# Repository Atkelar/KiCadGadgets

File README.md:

# KiCadGadgets
Some misc projects made in KiCad that didn't require individual repositories...

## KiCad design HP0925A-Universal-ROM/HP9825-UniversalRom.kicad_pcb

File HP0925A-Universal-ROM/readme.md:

# Universal ROM Cartridge

This project is a KiCAD drawing for a universal ROM cartridge. It consists of address latches and decoders, a DIP switch block and two EEPROMs. The idea is to have all the option ROMs that the 9825 had on one cartridge - pretty much like the "B" model had - but still inside the regular expansion slot. This way, one can "emulate" any configuration of option ROMs at the push of a button....

## challenges...

After finally getting the "card enable" line set up correct in "Rev.B", I still couldn't get it to work. And even reading back the ROM had all sorts of weird results... 

 1. the first problem was my ROM reader adapter... I hooked up the IDA-Bits 8-15 in reverse, so naturally, the results were a bit... fragmented.

 2. the second issue is pretty much caused by HP. They have put a set of bus transceivers in between the system IDA bus and the expansion slots. Those decouple all 16 IDA bus lines, but all other signals are passed in "as is". No bit deal. But somewhere it seems to have gotten lost, that these are INVERTING TRANSCEIVERS! So both address and data arrive and go out from the option ROMs in a "positive logic" fashion. I set up my ROMs to handle the reversed and inverted bit pattern that the system ROM needs, so again: didn't *quite* work as expected. And that took some time to find out...

Anyhow: it works now! My system is running on an almost full complement of ROM cartridges! All I'm missing is the "mass storage" (aka "disk IO") ROM... anybody got a source of that somewhere?

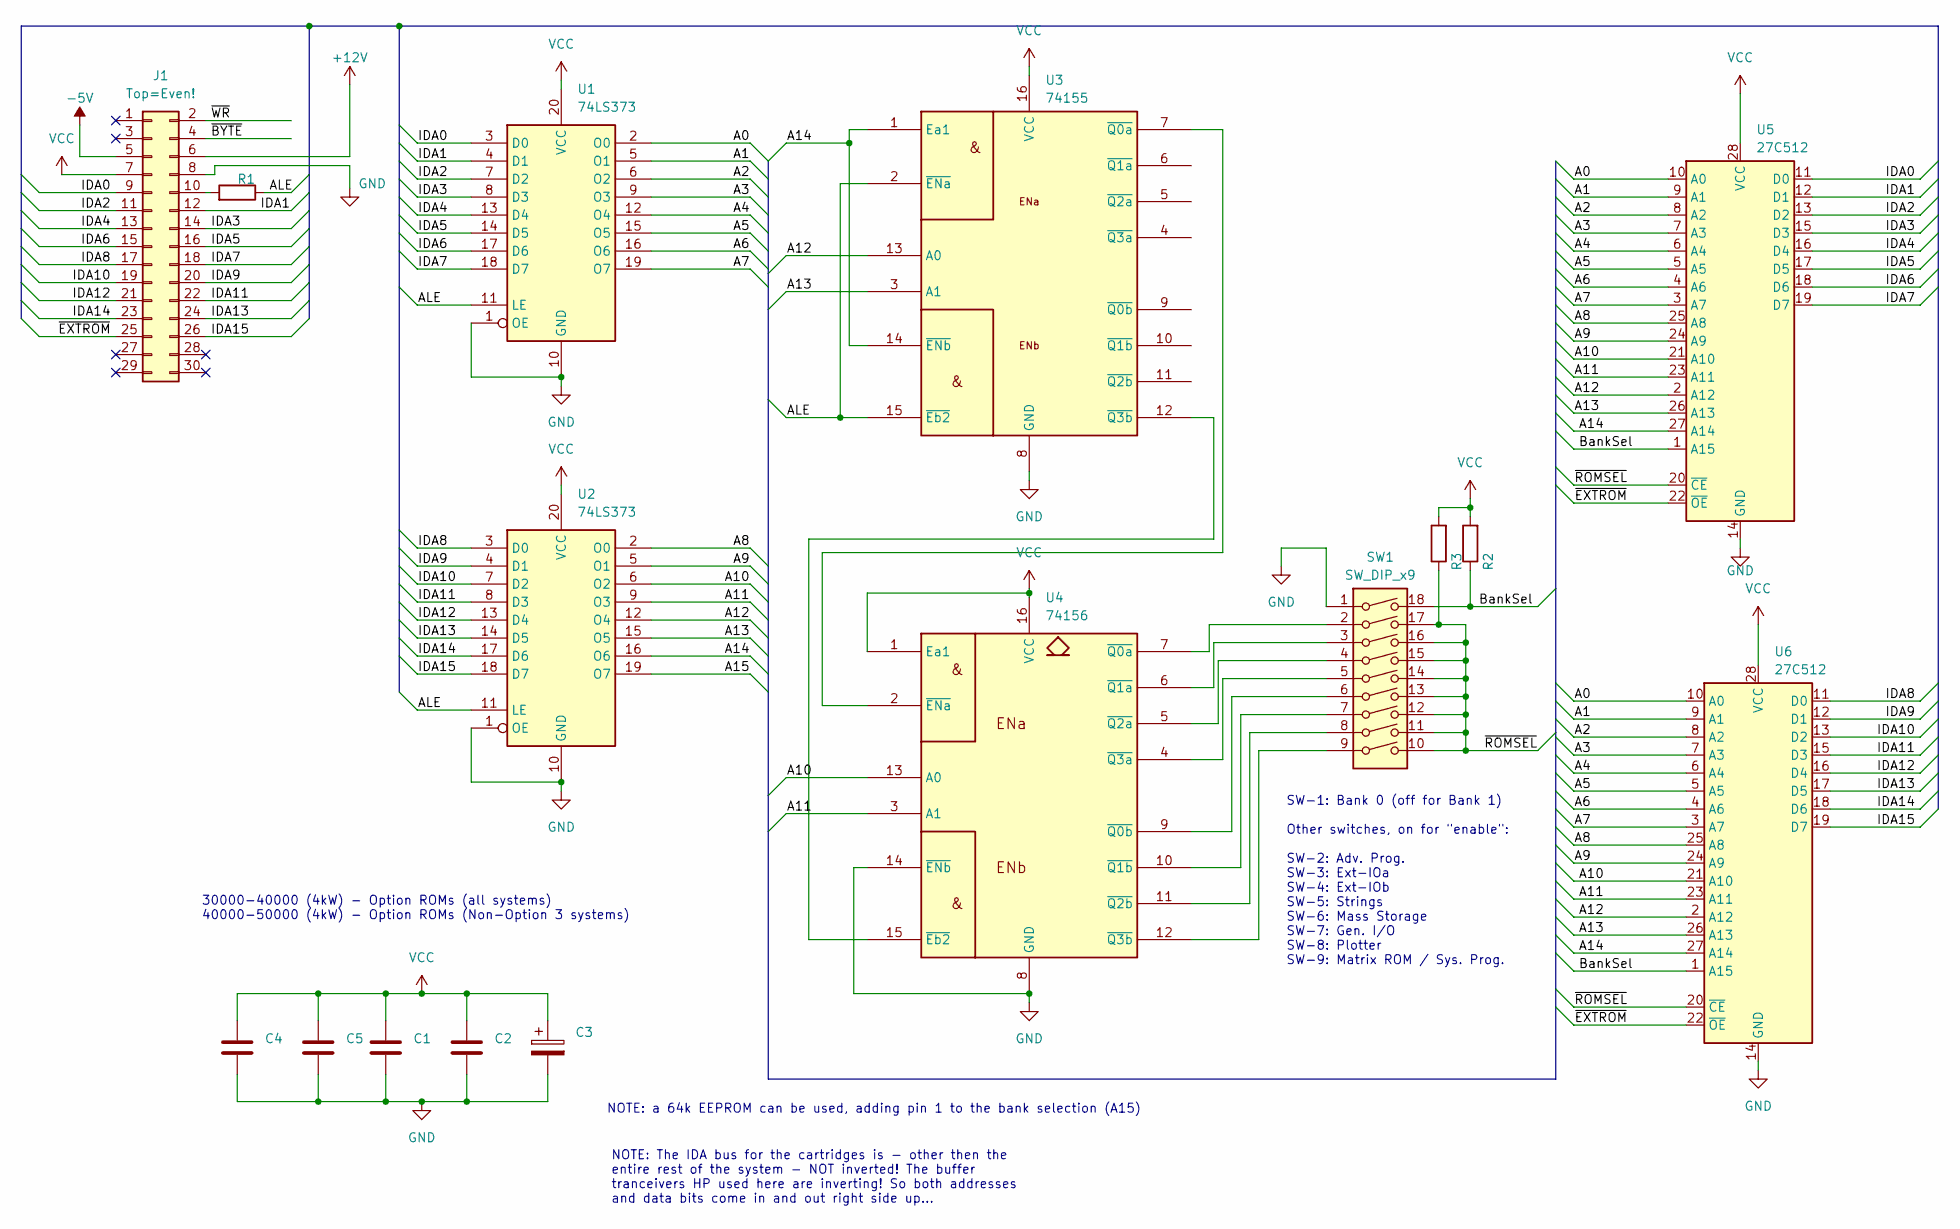
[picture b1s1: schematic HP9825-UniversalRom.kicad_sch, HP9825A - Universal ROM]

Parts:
C1, C2, C4, C5: C; C_Disc_D5.1mm_W3.2mm_P5.00mm
C3: CP_Axial_L11.0mm_D5.0mm_P18.00mm_Horizontal
J1: Top=Even!; 9825A-MemoryModule
R1: 16; R_Axial_DIN0207_L6.3mm_D2.5mm_P10.16mm_Horizontal
R2, R3: 3k3; R_Axial_DIN0207_L6.3mm_D2.5mm_P10.16mm_Horizontal
SW1: SW_DIP_x9; SW_DIP_SPSTx09_Slide_6.7x24.42mm_W7.62mm_P2.54mm_LowProfile
U1, U2: 74LS373; DIP-20_W7.62mm
U3: 74155; DIP-16_W7.62mm
U4: 74156; DIP-16_W7.62mm
U5, U6: 27C512; DIP-28_W15.24mm

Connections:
+12V: J1.6
-5V: J1.5
/A0: U1.2 (O0), U5.10 (A0), U6.10 (A0)
/A1: U1.5 (O1), U5.9 (A1), U6.9 (A1)
/A2: U1.6 (O2), U5.8 (A2), U6.8 (A2)
/A3: U1.9 (O3), U5.7 (A3), U6.7 (A3)
/A4: U1.12 (O4), U5.6 (A4), U6.6 (A4)
/A5: U1.15 (O5), U5.5 (A5), U6.5 (A5)
/A6: U1.16 (O6), U5.4 (A6), U6.4 (A6)
/A7: U1.19 (O7), U5.3 (A7), U6.3 (A7)
/A8: U2.2 (O0), U5.25 (A8), U6.25 (A8)
/A9: U2.5 (O1), U5.24 (A9), U6.24 (A9)
/A10: U2.6 (O2), U4.13 (A0), U5.21 (A10), U6.21 (A10)
/A11: U2.9 (O3), U4.3 (A1), U5.23 (A11), U6.23 (A11)
/A12: U2.12 (O4), U3.13 (A0), U5.2 (A12), U6.2 (A12)
/A13: U2.15 (O5), U3.3 (A1), U5.26 (A13), U6.26 (A13)
/A14: U2.16 (O6), U3.1 (Ea1), U3.14 (~ENb), U5.27 (A14), U6.27 (A14)
/A15: U2.19 (O7)
/ALE: R1.1, U1.11 (LE), U2.11 (LE), U3.2 (~ENa), U3.15 (~Eb2)
/BankSel: R2.1, SW1.18, U5.1 (A15), U6.1 (A15)
/IDA0: J1.9, U1.3 (D0), U5.11 (D0)
/IDA1: J1.12, U1.4 (D1), U5.12 (D1)
/IDA2: J1.11, U1.7 (D2), U5.13 (D2)
/IDA3: J1.14, U1.8 (D3), U5.15 (D3)
/IDA4: J1.13, U1.13 (D4), U5.16 (D4)
/IDA5: J1.16, U1.14 (D5), U5.17 (D5)
/IDA6: J1.15, U1.17 (D6), U5.18 (D6)
/IDA7: J1.18, U1.18 (D7), U5.19 (D7)
/IDA8: J1.17, U2.3 (D0), U6.11 (D0)
/IDA9: J1.20, U2.4 (D1), U6.12 (D1)
/IDA10: J1.19, U2.7 (D2), U6.13 (D2)
/IDA11: J1.22, U2.8 (D3), U6.15 (D3)
/IDA12: J1.21, U2.13 (D4), U6.16 (D4)
/IDA13: J1.24, U2.14 (D5), U6.17 (D5)
/IDA14: J1.23, U2.17 (D6), U6.18 (D6)
/IDA15: J1.26, U2.18 (D7), U6.19 (D7)
/~BYTE: J1.4
/~EXTROM: J1.25, U5.22 (~OE), U6.22 (~OE)
/~ROMSEL: R3.1, SW1.10, SW1.11, SW1.12, SW1.13, SW1.14, SW1.15, SW1.16, SW1.17, U5.20 (~CE), U6.20 (~CE)
/~WR: J1.2
GND: C1.2, C2.2, C3.2, C4.2, C5.2, J1.8, SW1.1, U1.1 (OE), U1.10 (GND), U2.1 (OE), U2.10 (GND), U3.8 (GND), U4.8 (GND), U4.14 (~ENb), U5.14 (GND), U6.14 (GND)
unnamed: J1.10, R1.2
unnamed: U3.7 (~Q0a), U4.2 (~ENa)
unnamed: U3.12 (~Q3b), U4.15 (~Eb2)
unnamed: SW1.2, U4.7 (~Q0a)
unnamed: SW1.6, U4.9 (~Q0b)
unnamed: SW1.3, U4.6 (~Q1a)
unnamed: SW1.7, U4.10 (~Q1b)
unnamed: SW1.4, U4.5 (~Q2a)
unnamed: SW1.8, U4.11 (~Q2b)
unnamed: SW1.5, U4.4 (~Q3a)
unnamed: SW1.9, U4.12 (~Q3b)
VCC: C1.1, C2.1, C3.1, C4.1, C5.1, J1.7, R2.2, R3.2, U1.20 (VCC), U2.20 (VCC), U3.16 (VCC), U4.1 (Ea1), U4.16 (VCC), U5.28 (VCC), U6.28 (VCC)

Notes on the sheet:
30000-40000 (4kW) - Option ROMs (all systems) 40000-50000 (4kW) - Option ROMs (Non-Option 3 systems)
NOTE: a 64k EEPROM can be used, adding pin 1 to the bank selection (A15)
SW-1: Bank 0 (off for Bank 1) Other switches, on for "enable": SW-2: Adv. Prog. SW-3: Ext-IOa SW-4: Ext-IOb SW-5: Strings SW-6: Mass Storage SW-7: Gen. I/O SW-8: Plotter SW-9: Matrix ROM / Sys. Prog.
NOTE: The IDA bus for the cartridges is - other then the entire rest of the system - NOT inverted! The buffer tranceivers HP used here are inverting! So both addresses and data bits come in and out right side up...

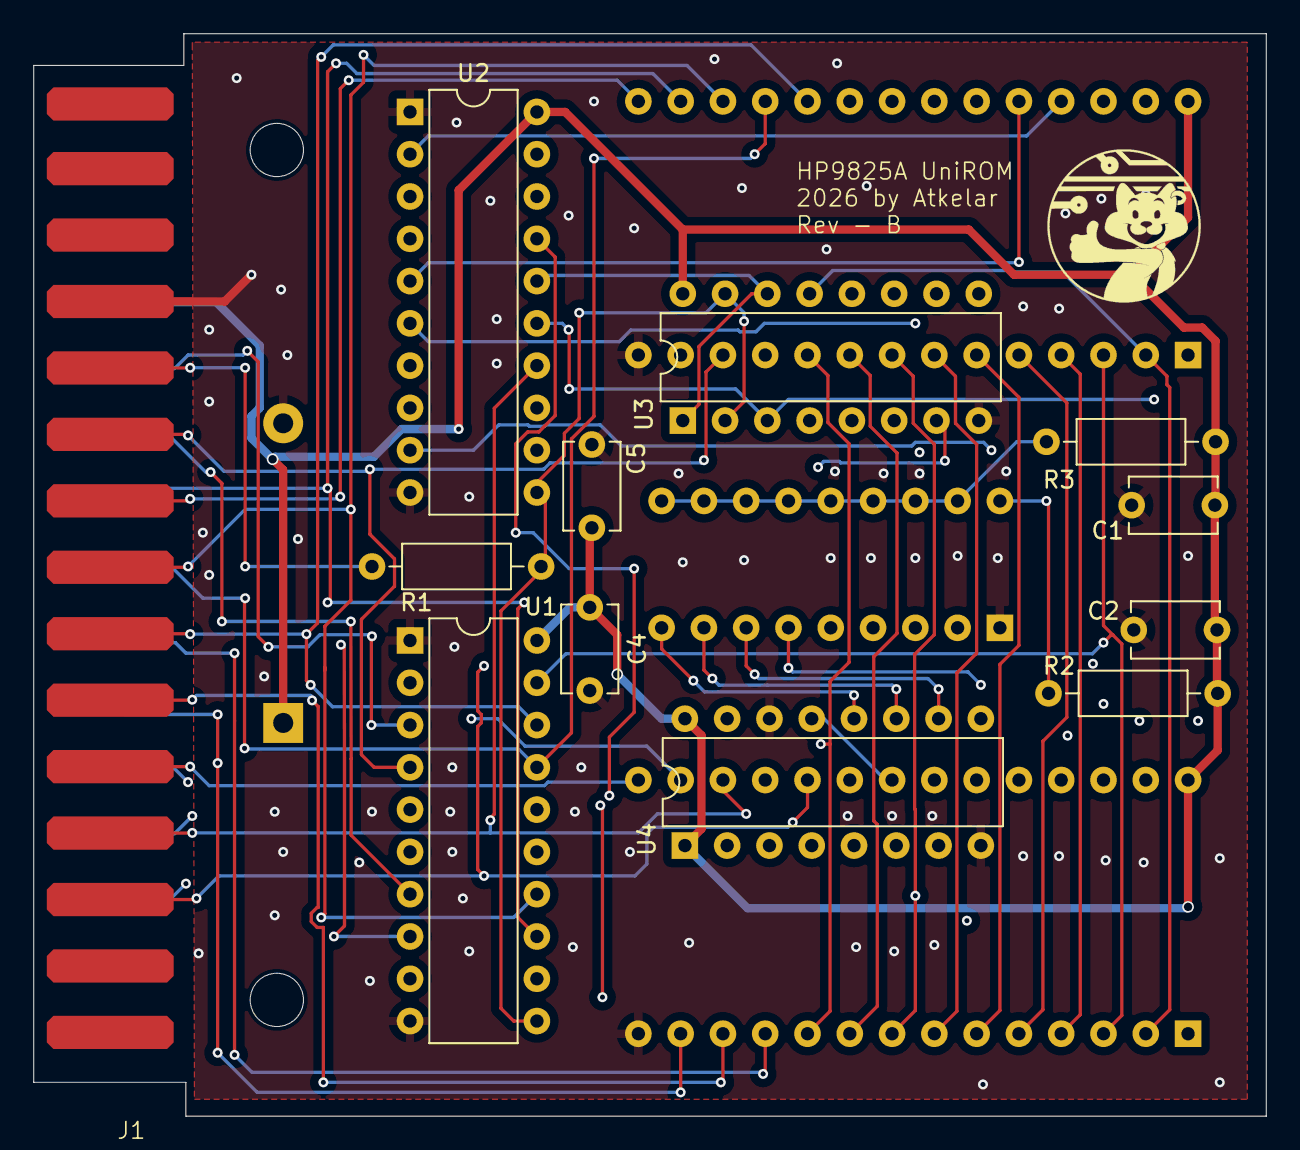
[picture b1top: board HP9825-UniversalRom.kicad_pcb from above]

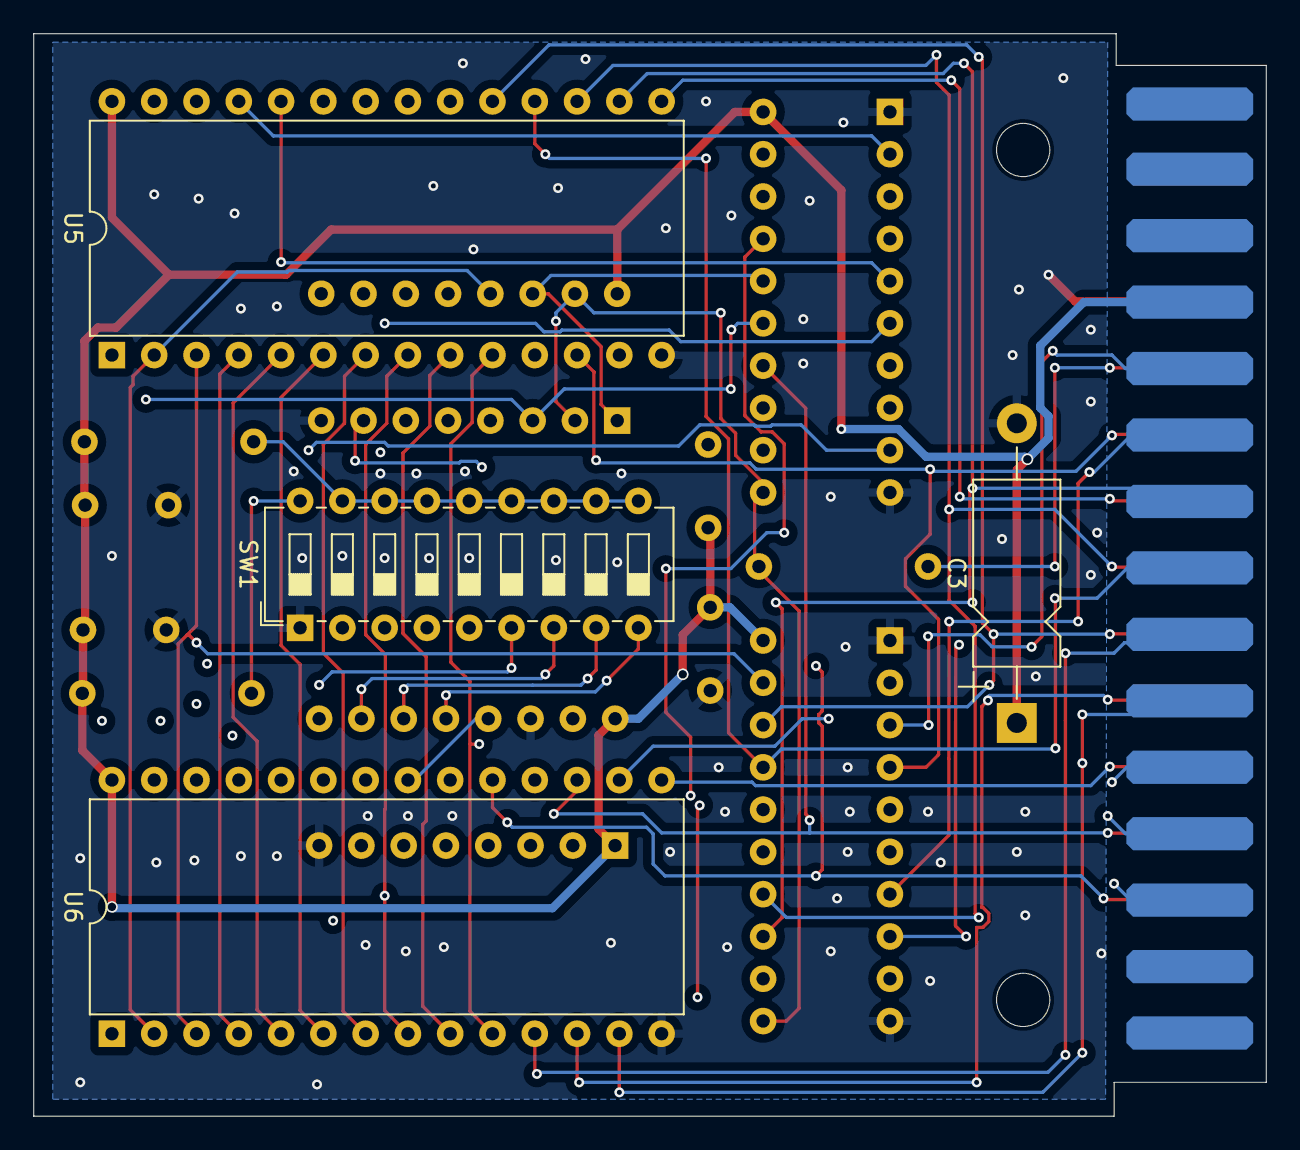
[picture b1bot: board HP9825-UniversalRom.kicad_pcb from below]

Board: 4 copper layers, 74.0 x 65.0 mm, 16 parts (4 on the bottom side), 48 nets.

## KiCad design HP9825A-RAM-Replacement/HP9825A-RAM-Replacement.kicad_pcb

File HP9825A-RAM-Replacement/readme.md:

# HP9825A RAM Replacement

The HP9825A "calculator"[^1] is a pretty useful machine for controlling various lab related devices, mostly but not exclusively vie the HP-IB bus. When it originally was designed, it came with a base contingent of 8k of RAM, arranged in 4k words. For a calculator that is controlling a few measurements, this seemed plenty. But naturally, requirements grew and so even the base unit offered expansions to 16k or even 24k of RAM, by means of adding a second 8k or 16k RAM PCB to the existing 8k one. Problematic here is that these RAM chips are DRAMs that are aging by now and getting hard to replace. Mostly because while the are using a 5V operating voltage, they want their CS line driven by 12V and also need a -5V bias voltage. These type of chips haven't been made in ages. Another quirk is that they have inputs and outputs on different pins *AND* different polarity: i.e. the input is normal the output is inverted. So between the chip and the bus needs to be a non-inverting buffer (or none at all) in one direction and an inverting one in the other, or else all the bits will appear flipped.

That being said: my own 9825 was acting a bit weird, even after I fixed one of the three RAM PCBs I had and while it was mostly working, it did show signs of instability. My toughts were: the RAM is going bad. Note that so far, this hasn't been confirmed yet; another possible issue presented itself but that is another project. The suspicion was just the motivation behind this project.

## Idea...

These days, we can get SRAM chips with 64k or more a dime a dozen almost. And they are fast enough to run at the 6MHz clock speed. So... why even use DRAM? Back in the day, it was mostly cost and power requirements. But when I look at the 400mA draw on the 12V rail that just hte chip select lines need... brrr! *ANY* modern SRAM will outperform these old chips by a longshot. And it would also eliminate the refresh logic required and possibly the refresh-collision wait states. So: win-win-win-win... I'll take it!

## Process...

Decoding the various schematic versions that are out there, along with the original patent and CPU documentation I'm pretty sure I have nailed down the way the memory cycle works and can confidentally rip out about 50% of the support chips that only deal with the refresh logic.

The latest circuit design went to the breadboard!

...and from there to a PCB prototype!

And: ta-da! It works!

Note that there is an unpopulated chip on the board... that is a leftover from the process that I missed; unused chip that got removed and I didn't remove it from the PCB. Whoops. Revision B here has that fixed.

## Configuration!

The address space of the 9825 is a 15-bit word space. I.e. 32k 2-byte addresses for a grand total of 64k byte. It's a bit of a twist to think in words when you are used to bytes, but this is how it works. Also, that memory space is strictly divided into the lower range for ROMs and the upper range for RAM. The CPU demands that the upper edge of addressable memory is RAM; it puts some floating point registeres there that can't be moved. The system ROM also puts all its core variables and the call stack there. This is why the upper 8k bytes are fixed on my replacement baord. It will *always* react to that. Then, you can add more 8k blocks from top to bottom to get 16, 24 and 32 kbytes of RAM. This setting has to be mirrored by the DIP switches on the CPU PCB, since those will prevent the "STM" signal to reach the RAM at all otherwise.

The important side note is: the expansion ROMs[^2] are hard coded to specific addresses. And that means that the 24kbyte version is the maximum RAM that can still use all the available expansion modules. The 32k version has a few no-go expansion modules and mixing these might cause damage to the circuitry. I'm keeping mine at 24k for that reason!

## Possible optimization?

I am not 100% sure if the "MEB" signal needs to be handled at all - it is "memory busy" I'd guess, to signal the CPU that the RAM isn't ready to process the request. It is tied to the refresh cycle and other elements, so I kept it. Since it's open collector, it should be easy enough to test: disconect the bus line and see if it still works, but right now, I'm too happy that it works at all to try something crazy like this!

[^1]: later model revisions did use the term "computer", but this is specifically for the base model "A", so I'll call it calculator anyhow
[^2]: which are a must have!

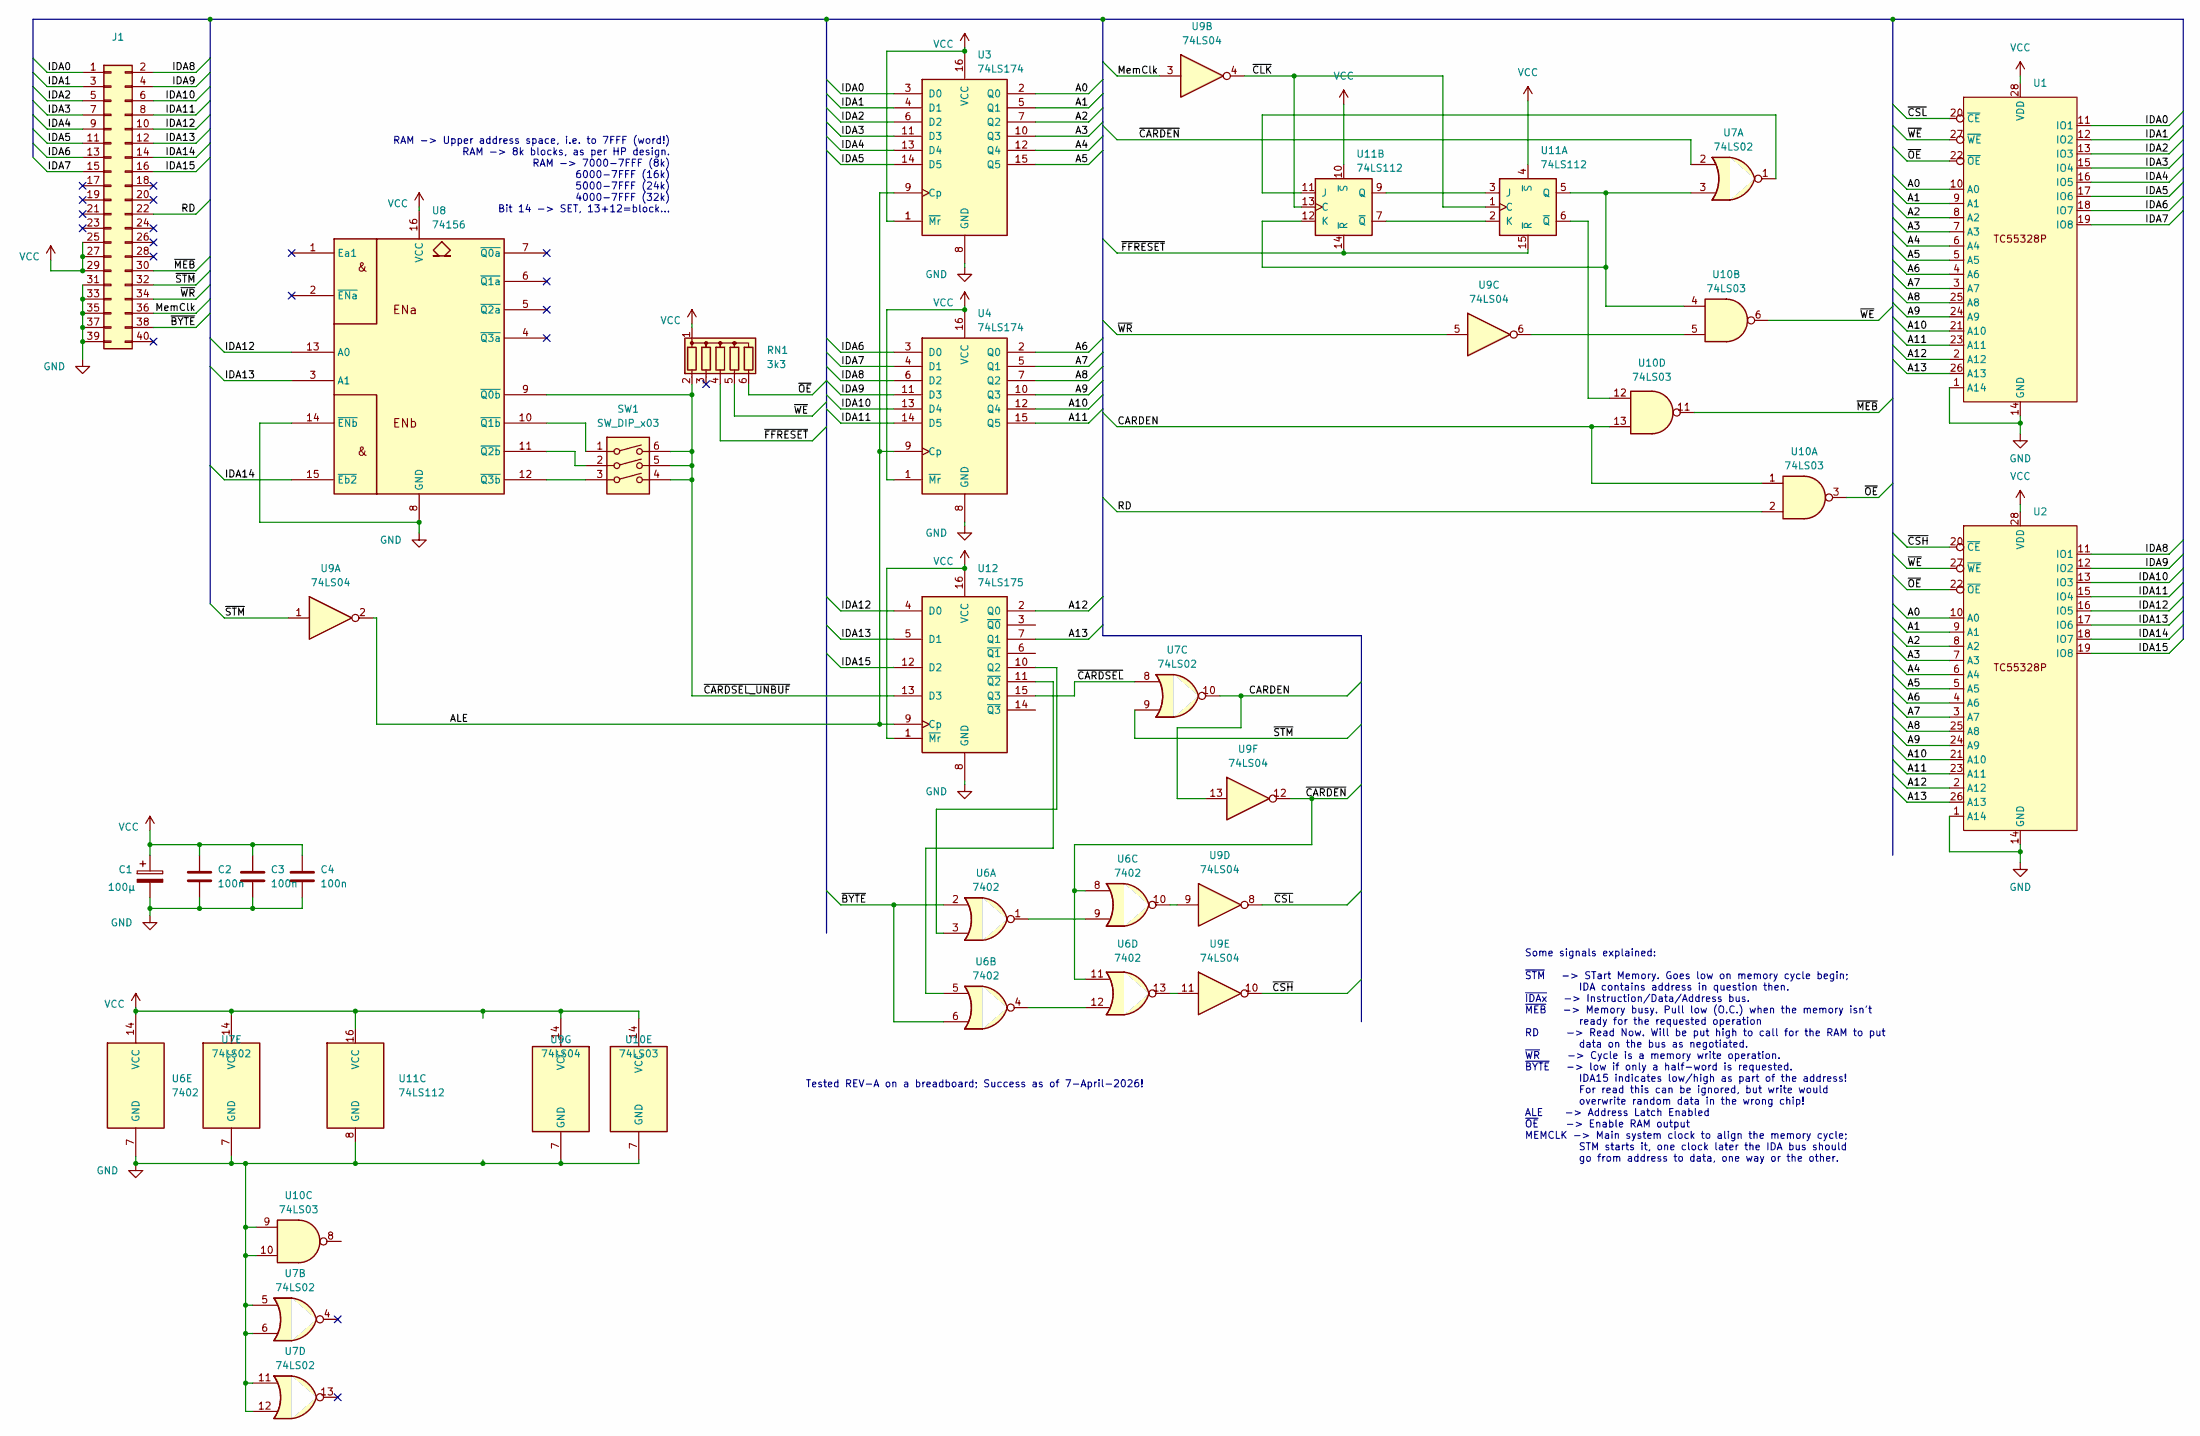
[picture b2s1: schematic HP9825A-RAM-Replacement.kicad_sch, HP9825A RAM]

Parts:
C1: 100µ; CP_Axial_L18.0mm_D10.0mm_P25.00mm_Horizontal
C2, C3, C4: 100n; C_Disc_D4.7mm_W2.5mm_P5.00mm
J1: Conn_02x20_Odd_Even; 9825A-RAM-CE
RN1: 3k3; R_Array_SIP6
SW1: SW_DIP_x03; SW_DIP_SPSTx03_Slide_9.78x9.8mm_W7.62mm_P2.54mm
U1, U2: DIP-28_W7.62mm
U3, U4: 74LS174; DIP-16_W7.62mm
U6: 7402; DIP-14_W7.62mm
U7: 74LS02; DIP-14_W7.62mm
U8: 74156; DIP-16_W7.62mm
U9: 74LS04; DIP-14_W7.62mm
U10: 74LS03; DIP-14_W7.62mm
U11: 74LS112; DIP-16_W7.62mm
U12: 74LS175; DIP-16_W7.62mm

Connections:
/A0: U1.10 (A0), U2.10 (A0), U3.2 (Q0)
/A1: U1.9 (A1), U2.9 (A1), U3.5 (Q1)
/A2: U1.8 (A2), U2.8 (A2), U3.7 (Q2)
/A3: U1.7 (A3), U2.7 (A3), U3.10 (Q3)
/A4: U1.6 (A4), U2.6 (A4), U3.12 (Q4)
/A5: U1.5 (A5), U2.5 (A5), U3.15 (Q5)
/A6: U1.4 (A6), U2.4 (A6), U4.2 (Q0)
/A7: U1.3 (A7), U2.3 (A7), U4.5 (Q1)
/A8: U1.25 (A8), U2.25 (A8), U4.7 (Q2)
/A9: U1.24 (A9), U2.24 (A9), U4.10 (Q3)
/A10: U1.21 (A10), U2.21 (A10), U4.12 (Q4)
/A11: U1.23 (A11), U2.23 (A11), U4.15 (Q5)
/A12: U1.2 (A12), U2.2 (A12), U12.2 (Q0)
/A13: U1.26 (A13), U2.26 (A13), U12.7 (Q1)
/ALE: U3.9 (Cp), U4.9 (Cp), U9.2, U12.9 (Cp)
/CARDEN: U7.10, U9.13, U10.1, U10.13
/IDA0: J1.1, U1.11 (IO1), U3.3 (D0)
/IDA1: J1.3, U1.12 (IO2), U3.4 (D1)
/IDA2: J1.5, U1.13 (IO3), U3.6 (D2)
/IDA3: J1.7, U1.15 (IO4), U3.11 (D3)
/IDA4: J1.9, U1.16 (IO5), U3.13 (D4)
/IDA5: J1.11, U1.17 (IO6), U3.14 (D5)
/IDA6: J1.13, U1.18 (IO7), U4.3 (D0)
/IDA7: J1.15, U1.19 (IO8), U4.4 (D1)
/IDA8: J1.2, U2.11 (IO1), U4.6 (D2)
/IDA9: J1.4, U2.12 (IO2), U4.11 (D3)
/IDA10: J1.6, U2.13 (IO3), U4.13 (D4)
/IDA11: J1.8, U2.15 (IO4), U4.14 (D5)
/IDA12: J1.10, U2.16 (IO5), U8.13 (A0), U12.4 (D0)
/IDA13: J1.12, U2.17 (IO6), U8.3 (A1), U12.5 (D1)
/IDA14: J1.14, U2.18 (IO7), U8.15 (~Eb2)
/IDA15: J1.16, U2.19 (IO8), U12.12 (D2)
/MemClk: J1.36, U9.3
/RD: J1.22, U10.2
/RDY: J1.30, U10.11
/~BYTE: J1.38, U6.2, U6.6
/~CARDEN: U6.8, U6.11, U7.2, U9.12
/~CARDSEL_UNBUF: RN1.2 (R1), SW1.4, SW1.5, SW1.6, U8.9 (~Q0b), U12.13 (D3)
/~CARDSEL: U7.8, U12.15 (Q3)
/~CLK: U9.4, U11.1 (C), U11.13 (C)
/~CSH: U2.20 (~CE), U9.10
/~CSL: U1.20 (~CE), U9.8
/~FFRESET: RN1.4 (R3), U11.14 (~R), U11.15 (~R)
/~OE: RN1.6 (R5), U1.22 (~OE), U2.22 (~OE), U10.3
/~STM: J1.32, U7.9, U9.1
/~WE: RN1.5 (R4), U1.27 (~WE), U2.27 (~WE), U10.6
/~WR: J1.34, U9.5
GND: C1.2, C2.2, C3.2, C4.2, J1.31, J1.33, J1.35, J1.37, J1.39, U1.1 (A14), U1.14 (GND), U2.1 (A14), U2.14 (GND), U3.8 (GND), U4.8 (GND), U6.7 (GND), U7.5, U7.6, U7.7 (GND), U7.11, U7.12, U8.8 (GND), U8.14 (~ENb), U9.7 (GND), U10.7 (GND), U10.9, U10.10, U11.8 (GND), U12.8 (GND)
unnamed: U6.1, U6.9
unnamed: U6.10, U9.9
unnamed: U6.4, U6.12
unnamed: U6.13, U9.11
unnamed: SW1.1, U8.10 (~Q1b)
unnamed: SW1.2, U8.11 (~Q2b)
unnamed: SW1.3, U8.12 (~Q3b)
unnamed: U9.6, U10.5
unnamed: U11.3 (J), U11.9 (Q)
unnamed: U11.2 (K), U11.7 (~Q)
unnamed: U7.3, U10.4, U11.5 (Q), U11.12 (K)
unnamed: U10.12, U11.6 (~Q)
unnamed: U7.1, U11.11 (J)
unnamed: U6.3, U12.10 (Q2)
unnamed: U6.5, U12.11 (~Q2)
VCC: C1.1, C2.1, C3.1, C4.1, J1.25, J1.27, J1.29, RN1.1 (common), U1.28 (VDD), U2.28 (VDD), U3.1 (~Mr), U3.16 (VCC), U4.1 (~Mr), U4.16 (VCC), U6.14 (VCC), U7.14 (VCC), U8.16 (VCC), U9.14 (VCC), U10.14 (VCC), U11.4 (~S), U11.10 (~S), U11.16 (VCC), U12.1 (~Mr), U12.16 (VCC)

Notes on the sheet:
RAM -> Upper address space, i.e. to 7FFF (word!) RAM -> 8k blocks, as per HP design. RAM -> 7000-7FFF (8k) 6000-7FFF (16k) 5000-7FFF (24k) 4000-7FFF (32k) Bit 14 -> SET, 13+12=block...
Tested REV-A on a breadboard; Success as of 7-April-2026!
Some signals explained: ~{STM} -> STart Memory. Goes low on memory cycle begin; IDA contains address in question then. ~{IDAx} -> Instruction/Data/Address bus. ~{MEB} -> Memory busy. Pull low (O.C.) when the memory isn't ready for the requested operation RD -> Read Now. Will be put high to call for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

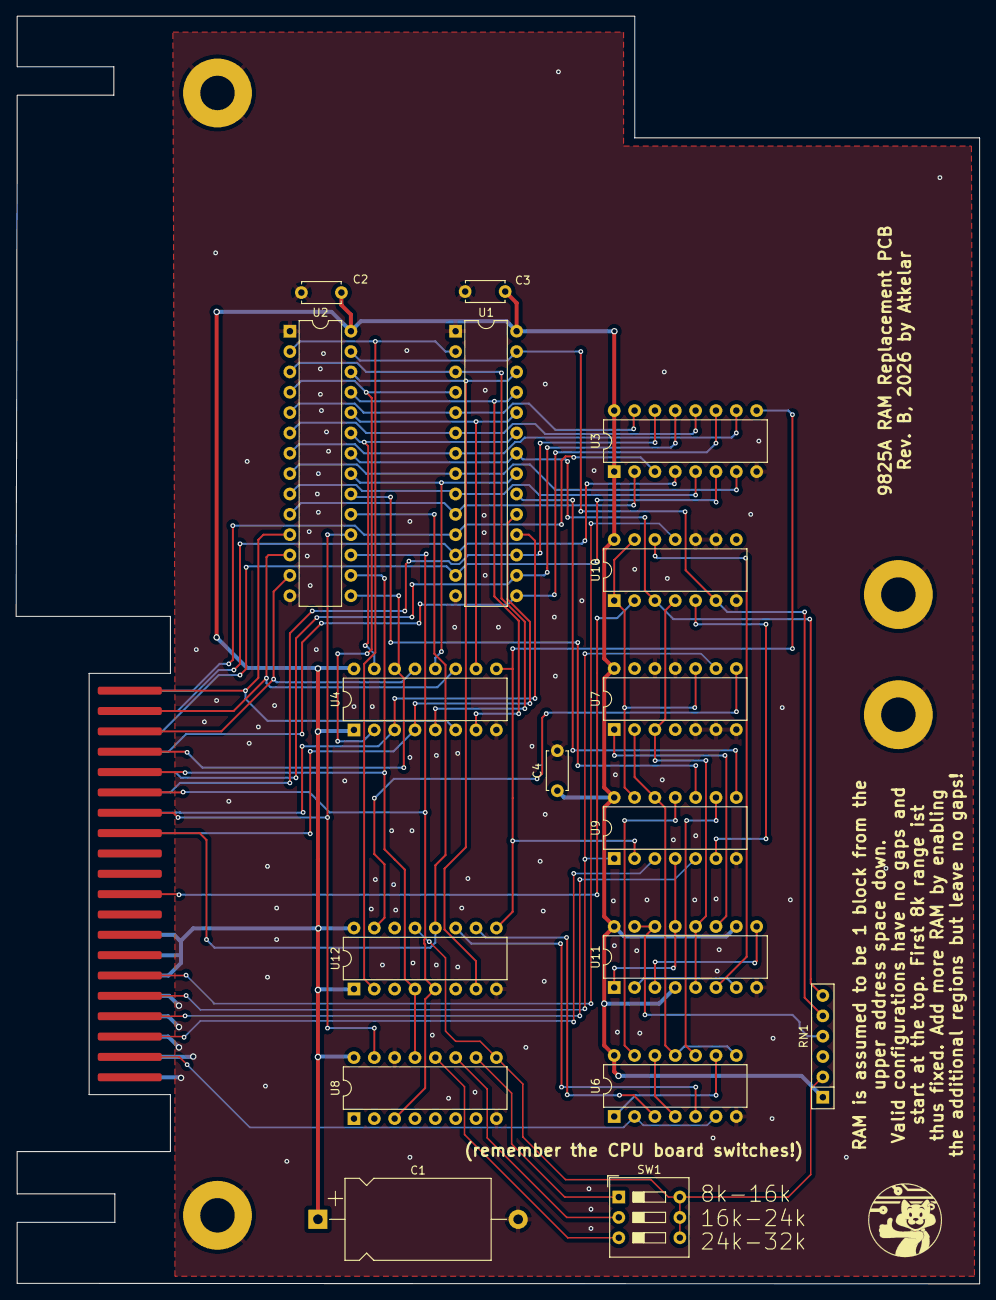
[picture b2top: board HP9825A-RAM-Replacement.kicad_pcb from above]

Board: 2 copper layers, 120.3 x 158.2 mm, 18 parts (0 on the bottom side), 64 nets.

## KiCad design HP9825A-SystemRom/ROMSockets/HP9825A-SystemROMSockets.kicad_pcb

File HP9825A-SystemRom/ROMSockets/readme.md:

# ROM Socket PCB

This PCB connects to the main PCB via 40-pin pin header, or just plain wires. It is required to offset the PCB to make room for the IC sockets and ROM chips.

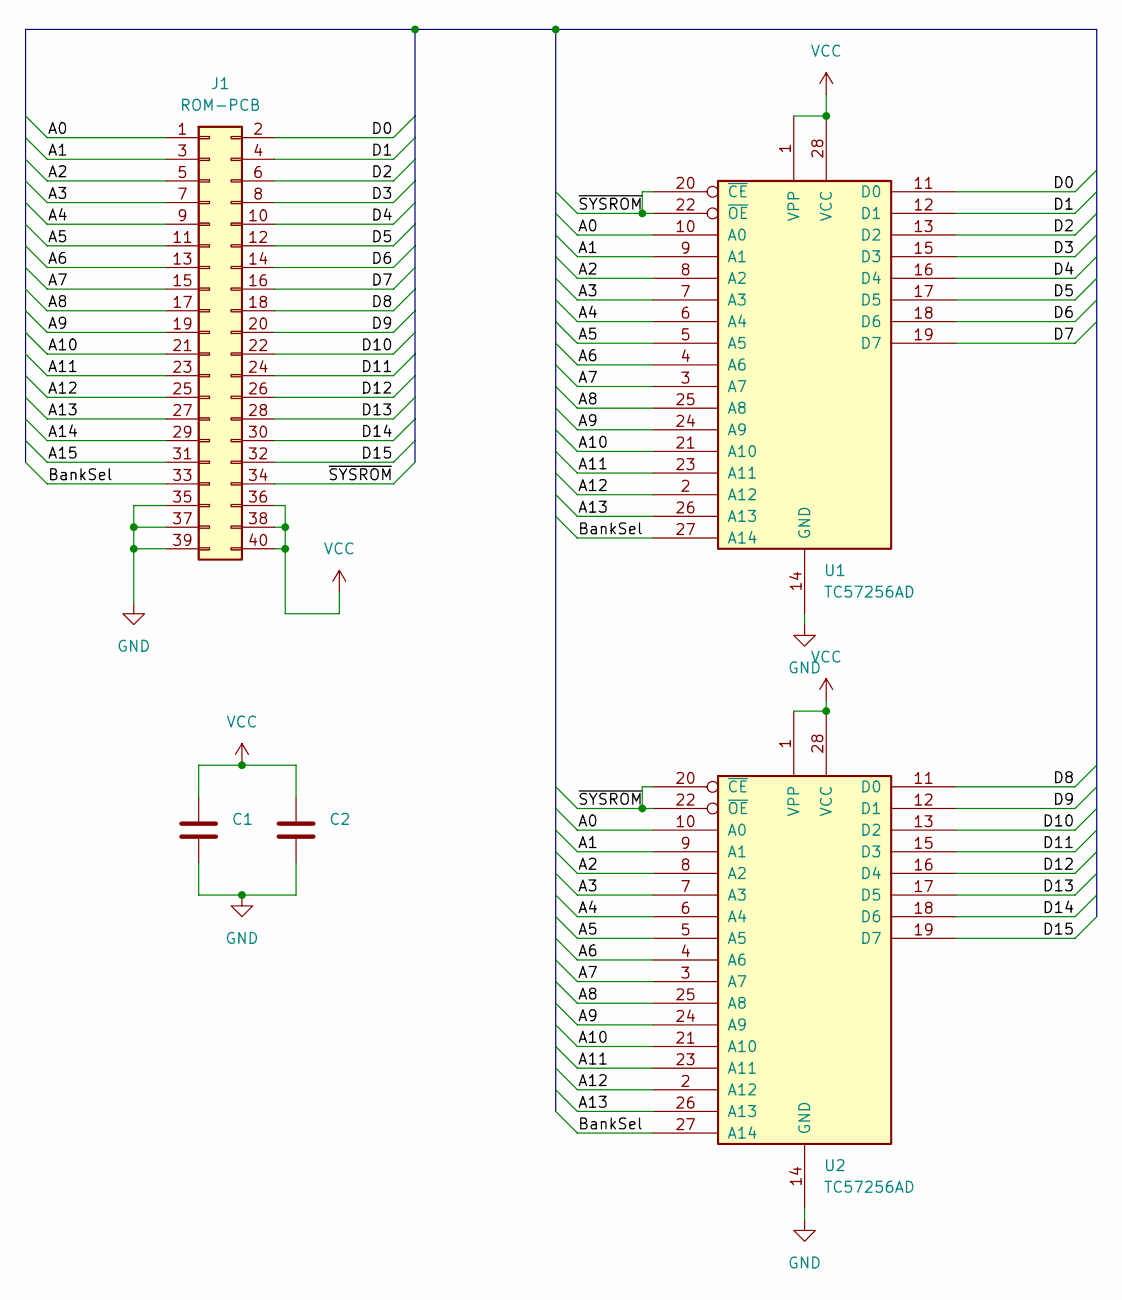
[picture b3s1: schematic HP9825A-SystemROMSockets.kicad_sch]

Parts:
C1, C2: C; C_Disc_D5.1mm_W3.2mm_P5.00mm
J1: ROM-PCB; PinHeader_2x20_P2.54mm_Vertical
U1, U2: TC57256AD; DIP-28_W15.24mm_LongPads

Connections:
/A0: J1.1, U1.10 (A0), U2.10 (A0)
/A1: J1.3, U1.9 (A1), U2.9 (A1)
/A2: J1.5, U1.8 (A2), U2.8 (A2)
/A3: J1.7, U1.7 (A3), U2.7 (A3)
/A4: J1.9, U1.6 (A4), U2.6 (A4)
/A5: J1.11, U1.5 (A5), U2.5 (A5)
/A6: J1.13, U1.4 (A6), U2.4 (A6)
/A7: J1.15, U1.3 (A7), U2.3 (A7)
/A8: J1.17, U1.25 (A8), U2.25 (A8)
/A9: J1.19, U1.24 (A9), U2.24 (A9)
/A10: J1.21, U1.21 (A10), U2.21 (A10)
/A11: J1.23, U1.23 (A11), U2.23 (A11)
/A12: J1.25, U1.2 (A12), U2.2 (A12)
/A13: J1.27, U1.26 (A13), U2.26 (A13)
/A14: J1.29
/A15: J1.31
/BankSel: J1.33, U1.27 (A14), U2.27 (A14)
/D0: J1.2, U1.11 (D0)
/D1: J1.4, U1.12 (D1)
/D2: J1.6, U1.13 (D2)
/D3: J1.8, U1.15 (D3)
/D4: J1.10, U1.16 (D4)
/D5: J1.12, U1.17 (D5)
/D6: J1.14, U1.18 (D6)
/D7: J1.16, U1.19 (D7)
/D8: J1.18, U2.11 (D0)
/D9: J1.20, U2.12 (D1)
/D10: J1.22, U2.13 (D2)
/D11: J1.24, U2.15 (D3)
/D12: J1.26, U2.16 (D4)
/D13: J1.28, U2.17 (D5)
/D14: J1.30, U2.18 (D6)
/D15: J1.32, U2.19 (D7)
/~SYSROM: J1.34, U1.20 (~CE), U1.22 (~OE), U2.20 (~CE), U2.22 (~OE)
GND: C1.2, C2.2, J1.35, J1.37, J1.39, U1.14 (GND), U2.14 (GND)
VCC: C1.1, C2.1, J1.36, J1.38, J1.40, U1.1 (VPP), U1.28 (VCC), U2.1 (VPP), U2.28 (VCC)

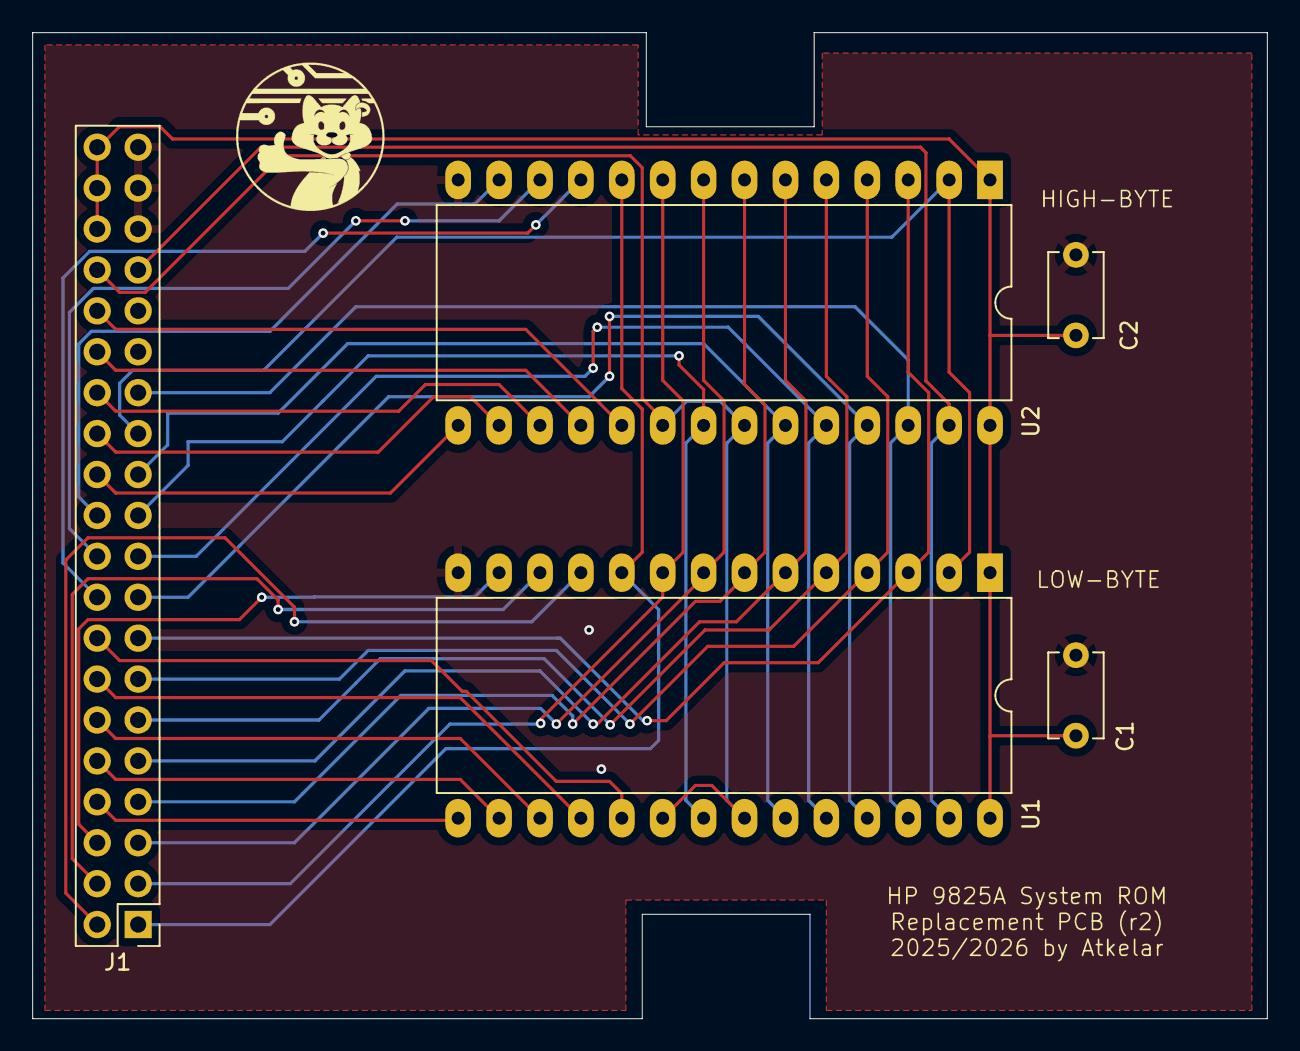
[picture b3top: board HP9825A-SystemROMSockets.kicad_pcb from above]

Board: 2 copper layers, 76.7 x 61.2 mm, 5 parts (0 on the bottom side), 34 nets.

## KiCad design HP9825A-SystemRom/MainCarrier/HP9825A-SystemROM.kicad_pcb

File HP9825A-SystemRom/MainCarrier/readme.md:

# Main Carrier PCB

This is the PCB for the logic ICs and the socket to connect to the ROM backplane.

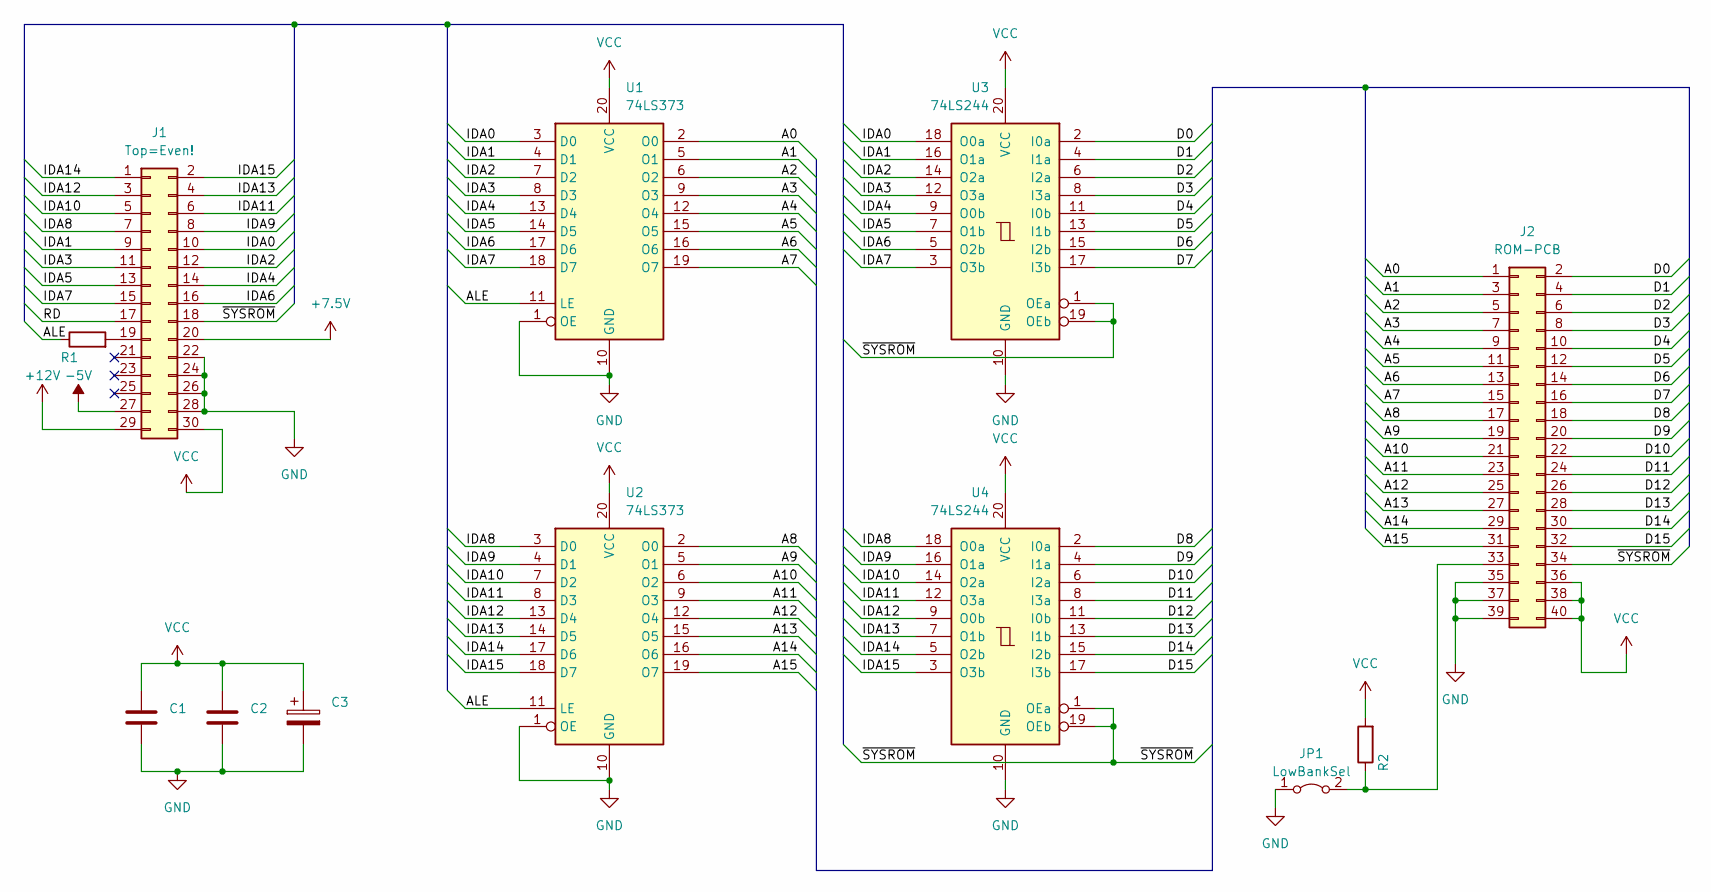
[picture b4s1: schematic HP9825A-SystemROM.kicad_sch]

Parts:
C1, C2: C; C_Disc_D5.1mm_W3.2mm_P5.00mm
C3: CP_Axial_L11.0mm_D5.0mm_P18.00mm_Horizontal
J1: Top=Even!; HP-Edge2
J2: ROM-PCB; PinHeader_2x20_P2.54mm_Vertical
JP1: LowBankSel; PinHeader_1x02_P2.54mm_Horizontal
R1, R2: R; R_Axial_DIN0207_L6.3mm_D2.5mm_P10.16mm_Horizontal
U1, U2: 74LS373; CERDIP-20_W7.62mm_SideBrazed_LongPads
U3, U4: 74LS244; CERDIP-20_W7.62mm_SideBrazed_LongPads

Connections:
+7.5V: J1.20
+12V: J1.29
-5V: J1.27
/A0: J2.1, U1.2 (O0)
/A1: J2.3, U1.5 (O1)
/A2: J2.5, U1.6 (O2)
/A3: J2.7, U1.9 (O3)
/A4: J2.9, U1.12 (O4)
/A5: J2.11, U1.15 (O5)
/A6: J2.13, U1.16 (O6)
/A7: J2.15, U1.19 (O7)
/A8: J2.17, U2.2 (O0)
/A9: J2.19, U2.5 (O1)
/A10: J2.21, U2.6 (O2)
/A11: J2.23, U2.9 (O3)
/A12: J2.25, U2.12 (O4)
/A13: J2.27, U2.15 (O5)
/A14: J2.29, U2.16 (O6)
/A15: J2.31, U2.19 (O7)
/ALE: R1.1, U1.11 (LE), U2.11 (LE)
/D0: J2.2, U3.2 (I0a)
/D1: J2.4, U3.4 (I1a)
/D2: J2.6, U3.6 (I2a)
/D3: J2.8, U3.8 (I3a)
/D4: J2.10, U3.11 (I0b)
/D5: J2.12, U3.13 (I1b)
/D6: J2.14, U3.15 (I2b)
/D7: J2.16, U3.17 (I3b)
/D8: J2.18, U4.2 (I0a)
/D9: J2.20, U4.4 (I1a)
/D10: J2.22, U4.6 (I2a)
/D11: J2.24, U4.8 (I3a)
/D12: J2.26, U4.11 (I0b)
/D13: J2.28, U4.13 (I1b)
/D14: J2.30, U4.15 (I2b)
/D15: J2.32, U4.17 (I3b)
/IDA0: J1.10, U1.3 (D0), U3.18 (O0a)
/IDA1: J1.9, U1.4 (D1), U3.16 (O1a)
/IDA2: J1.12, U1.7 (D2), U3.14 (O2a)
/IDA3: J1.11, U1.8 (D3), U3.12 (O3a)
/IDA4: J1.14, U1.13 (D4), U3.9 (O0b)
/IDA5: J1.13, U1.14 (D5), U3.7 (O1b)
/IDA6: J1.16, U1.17 (D6), U3.5 (O2b)
/IDA7: J1.15, U1.18 (D7), U3.3 (O3b)
/IDA8: J1.7, U2.3 (D0), U4.18 (O0a)
/IDA9: J1.8, U2.4 (D1), U4.16 (O1a)
/IDA10: J1.5, U2.7 (D2), U4.14 (O2a)
/IDA11: J1.6, U2.8 (D3), U4.12 (O3a)
/IDA12: J1.3, U2.13 (D4), U4.9 (O0b)
/IDA13: J1.4, U2.14 (D5), U4.7 (O1b)
/IDA14: J1.1, U2.17 (D6), U4.5 (O2b)
/IDA15: J1.2, U2.18 (D7), U4.3 (O3b)
/RD: J1.17
/~SYSROM: J1.18, J2.34, U3.1 (OEa), U3.19 (OEb), U4.1 (OEa), U4.19 (OEb)
GND: C1.2, C2.2, C3.2, J1.22, J1.24, J1.26, J1.28, J2.35, J2.37, J2.39, JP1.1 (A), U1.1 (OE), U1.10 (GND), U2.1 (OE), U2.10 (GND), U3.10 (GND), U4.10 (GND)
unnamed: J1.19, R1.2
unnamed: J2.33, JP1.2 (B), R2.1
VCC: C1.1, C2.1, C3.1, J1.30, J2.36, J2.38, J2.40, R2.2, U1.20 (VCC), U2.20 (VCC), U3.20 (VCC), U4.20 (VCC)
